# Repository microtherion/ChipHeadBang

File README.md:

# ChipHeadBang
Design for an USB to Serial converter with ICSP header for (slow) bitbang programming, based on the CH340G chip. See http://samelimmat.blogspot.com/2015/04/introducing-chipheadbang.html

While this seems to work pretty well, and the CH340G can be obtained extremely cheaply from sources such as 
AliExpress, driver support can be a bit iffy. For current versions of OS X, the vendor provided driver will 
cause kernel panics, and as far as I know, only this commercial alternative will work: https://www.mac-usb-serial.com 

Boards can be ordered at OSHPark: https://oshpark.com/shared_projects/xvqfIt55

<br />This work is licensed under a <a rel="license" href="http://creativecommons.org/licenses/by/4.0/">Creative Commons Attribution 4.0 International License</a>.

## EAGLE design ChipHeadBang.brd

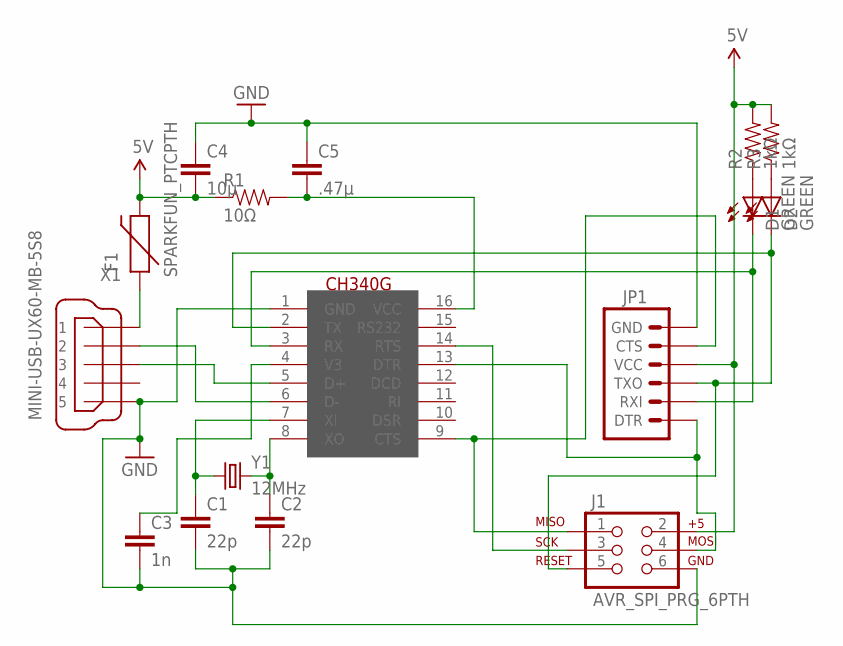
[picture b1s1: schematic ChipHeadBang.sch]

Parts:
C1, C2: 22p; 0603-CAP
C3: 1n; 0603-CAP
C4: 10µ; 0805
C5: .47µ; 0805
D1, D2: GREEN; LED-1206
F1: SPARKFUN_PTCPTH; SPARKFUN_PTC
J1: AVR_SPI_PRG_6PTH; 2X3
JP1: ARDUINO_SERIAL_PROGRAMPTH; 1X06
R1: 10Ω; 0603-RES
R2, R3: 1kΩ; 0603-RES
U$1: CH340G; SOIC16
X1: MINI-USB-UX60-MB-5S8; UX60-MB-5S8
Y1: 12MHz; SPARKFUN_HC49US

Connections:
5V: C4.2, F1.P$2 (2), J1.2, JP1.4 (VCC), R1.1, R2.2, R3.2
GND: C1.2, C2.2, C3.2, C4.1, C5.1, J1.6, JP1.6 (GND), U$1.1 (GND), X1.5
unnamed: F1.P$1 (1), X1.1
unnamed: U$1.6 (D-), X1.2
unnamed: U$1.5 (D+), X1.3
unnamed: C5.2, R1.2, U$1.16 (VCC)
unnamed: C1.1, U$1.7 (XI), Y1.1
unnamed: C2.1, U$1.8 (XO), Y1.2
unnamed: D1.A, R2.1
unnamed: J1.3, U$1.14 (RTS)
unnamed: C3.1, U$1.4 (V3)
unnamed: D1.C, JP1.2 (RXI), U$1.3 (RX)
unnamed: J1.1, JP1.5 (CTS), U$1.9 (CTS)
unnamed: D2.A, R3.1
unnamed: D2.C, J1.5, JP1.3 (TXO), U$1.2 (TX)
unnamed: J1.4, JP1.1 (DTR), U$1.13 (DTR)

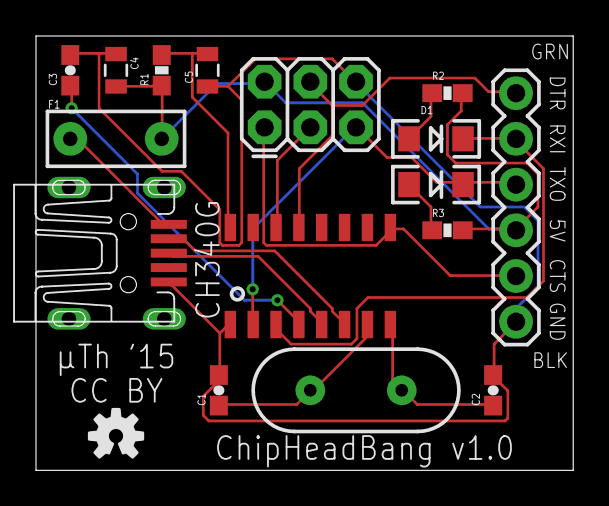
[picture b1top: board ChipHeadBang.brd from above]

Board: 2 copper layers, 29.8 x 24.1 mm, 17 parts (0 on the bottom side), 16 nets.

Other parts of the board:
U$2: OSHW-LOGO-S

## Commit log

2015-04-20 Moving ChipHeadBang to separate repo
2015-04-20 Added bill of materials
2015-04-20 Added pdf schematic
2015-04-20 Add license
2016-01-25 Add avrdude programmer entry
2016-01-25 Add baudrate, note about needing -i 300

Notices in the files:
ChipHeadBang.brd:
CC BY
parts and their libraries:
SparkFun-Passives: Licensing: CC v3.0 Share-Alike You are welcome to use this library for commercial purposes.
